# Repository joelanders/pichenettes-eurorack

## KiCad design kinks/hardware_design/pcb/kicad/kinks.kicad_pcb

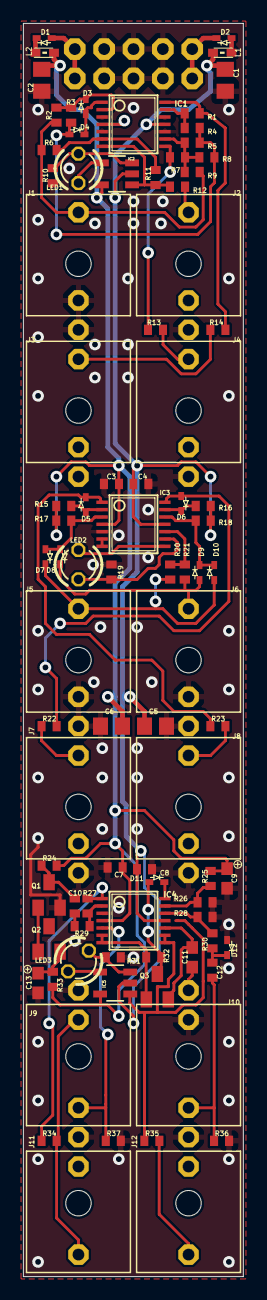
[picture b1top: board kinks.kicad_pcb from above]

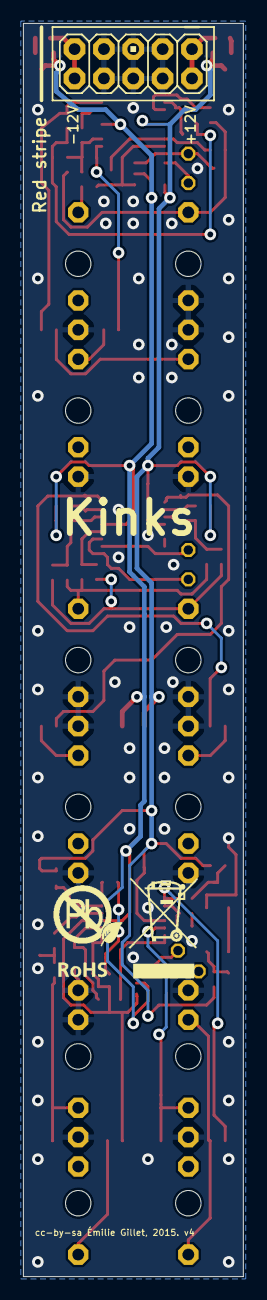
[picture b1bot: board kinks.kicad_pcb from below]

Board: 2 copper layers, 19.0 x 108.4 mm, 89 parts (2 on the bottom side), 56 nets.

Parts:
C1, C2, C5, C6: 22u; C0805
C3, C4, C7, C8, C10: 100n; C0402
C9, C13: 4.7u; C0603
C11: 10n; C0603
C12: 100p; C0402
D1, D2: PMEG2010AEB; SOD523
D3, D4, D5, D6, D7, D8, D9, D10, D11, D12: 1N4148; SOD523
IC1, IC3: TL074PW; TSSOP14
IC2, IC5: LM321MF; SOT23-5
IC4: OPA4171; TSSOP14
J1, J2, J3, J4, J5, J6, J7, J8, J9, J10, J11, J12: PJ301_THONKICONN6; WQP_PJ_301M6
JP1: M05X2PTH; AVR_ICSP
L1, L2: 0603
LED1, LED2, LED3: WP937EGW; LED3MM
Q1, Q2: MMBT3904; SOT23-BEC
Q3: MMBFJ309; SOT23
R1, R2, R6, R7, R9, R11: 200k; R0402
R3, R4, R5, R8, R28, R29, R36: 100k; R0402
R10, R19, R31: 1.0k; R0402
R12, R13, R14, R22, R23, R34, R35: 180; R0402
R15, R16, R17, R18: 220k; R0402
R20, R21, R25, R32, R37: 1.0M; R0402
R24: 4.7k; R0402
R26, R30: 10k; R0402
R27: 1.5M; R0402
R33: 470k; R0402
U$2: ROHS

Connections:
A: D7.C, D10.A, J5.P3, R20.2
B: D8.C, D9.A, J6.P3, R21.2
GND: C1.1, C2.2, C3.2, C4.1, C5.1, C6.2, C7.2, C8.1, C9.2, C11.2, C13.2, D12.A, IC1.3, IC1.5, IC1.10, IC1.12, IC3.5, IC4.3, J1.P1, J1.P2, J2.P1, J3.P1, J4.P1, J5.P1, J5.P2, J6.P1, J6.P2, J7.P1, J8.P1, J9.P1, J10.P1, J10.P2, J11.P1, J12.P1, JP1.3, JP1.4, JP1.5, JP1.6, JP1.7, JP1.8, Q1.E, R10.2, R19.2, R26.1, R28.1, R31.2, R36.1, R37.2
unnamed: D9.C, D10.C, IC3.12, R18.1
unnamed: D6.A, IC3.14, R22.2
unnamed: IC4.8, IC4.9, IC5.1, R35.2
unnamed: D6.C, IC3.13, R16.1
unnamed: D7.A, D8.A, IC3.3, R17.1
unnamed: D1.A, JP1.1, JP1.2
unnamed: IC3.6, IC3.7
unnamed: Q1.B, Q2.B
unnamed: IC2.3, LED1.K, R10.1
unnamed: D5.C, IC3.1, R23.2
unnamed: IC2.4, LED1.A
unnamed: C13.1, Q2.E, R33.2
unnamed: C10.2, R29.2
unnamed: IC3.8, LED2.K
unnamed: D5.A, IC3.2, R15.1
unnamed: IC4.2, R27.2, R29.1
unnamed: J8.P3, R23.1
unnamed: IC3.10, R20.1, R21.1
unnamed: IC5.3, LED3.A, R31.1
unnamed: D2.C, JP1.9, JP1.10
unnamed: IC1.6, R6.1, R11.2
unnamed: D1.C, L2.2
unnamed: IC1.7, IC2.1, R11.1, R12.2
unnamed: J2.P3, R12.1
unnamed: D3.C, IC1.2, R2.1, R3.2
unnamed: D3.A, D4.C, IC1.1
unnamed: IC1.14, R1.1, R14.2
unnamed: IC1.13, R1.2, R4.1
unnamed: IC3.9, LED2.A, R19.1
unnamed: IC5.4, LED3.K
unnamed: C10.1, Q1.C, R24.1
unnamed: J3.P3, R14.1
unnamed: IC1.9, R5.1, R7.2, R8.1, R9.1
unnamed: J4.P3, R13.1
unnamed: IC1.8, R7.1, R13.2
unnamed: IC4.1, R27.1, R34.2
unnamed: J9.P2, J11.P3, R34.1
unnamed: J1.P3, R2.2, R6.2, R9.2
unnamed: D4.A, R3.1, R4.2, R5.2, R8.2
unnamed: IC4.5, J9.P3, R37.1
unnamed: IC4.6, IC4.7, Q3.1, R32.2
unnamed: D11.A, Q3.3, R32.1
unnamed: D11.C, IC4.14
unnamed: D2.A, L1.2
unnamed: C11.1, IC4.10, Q3.2
unnamed: IC4.12, R28.2, R30.2
unnamed: J7.P3, R22.1
unnamed: J12.P3, R35.1
unnamed: C12.1, J10.P3, R36.2
unnamed: IC4.13, R25.1, R26.2
unnamed: C12.2, D12.C, R30.1
VCC: C2.1, C3.1, C6.1, C7.1, C9.1, IC1.4, IC2.5, IC3.4, IC4.4, IC5.5, L2.1, R15.2, R17.2, R24.2, R25.2, R33.1
VEE: C1.2, C4.2, C5.2, C8.2, IC1.11, IC2.2, IC3.11, IC4.11, IC5.2, L1.1, R16.2, R18.2

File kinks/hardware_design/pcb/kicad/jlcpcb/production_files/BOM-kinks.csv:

Comment,Designator,Footprint,LCSC
M05X2PTH,JP1,AVR_ICSP,
4.7u,C9,C0603,
PMEG2010AEB,D2,SOD523,
PMEG2010AEB,D1,SOD523,
WP937EGW,LED2,LED3MM,
1.0k,R19,R0402,
100n,C3,C0402,
100n,C4,C0402,
WP937EGW,LED3,LED3MM,
1.0k,R31,R0402,
LM321MF,IC5,SOT23-5,
100n,C7,C0402,
100n,C8,C0402,
PJ301_THONKICONN6,J1,WQP_PJ_301M6,
PJ301_THONKICONN6,J4,WQP_PJ_301M6,
PJ301_THONKICONN6,J2,WQP_PJ_301M6,
PJ301_THONKICONN6,J3,WQP_PJ_301M6,
PJ301_THONKICONN6,J8,WQP_PJ_301M6,
PJ301_THONKICONN6,J7,WQP_PJ_301M6,
PJ301_THONKICONN6,J5,WQP_PJ_301M6,
PJ301_THONKICONN6,J6,WQP_PJ_301M6,
PJ301_THONKICONN6,J12,WQP_PJ_301M6,
PJ301_THONKICONN6,J9,WQP_PJ_301M6,
PJ301_THONKICONN6,J10,WQP_PJ_301M6,
PJ301_THONKICONN6,J11,WQP_PJ_301M6,
TL074PW,IC3,TSSOP14,
1N4148,D10,SOD523,
1N4148,D9,SOD523,
220k,R18,R0402,
180,R22,R0402,
220k,R17,R0402,
180,R23,R0402,
1.0M,R20,R0402,
1.0M,R21,R0402,
WP937EGW,LED1,LED3MM,
1.0k,R10,R0402,
LM321MF,IC2,SOT23-5,
TL074PW,IC1,TSSOP14,
200k,R6,R0402,
200k,R11,R0402,
200k,R2,R0402,
100k,R3,R0402,
1N4148,D3,SOD523,
1N4148,D4,SOD523,
100k,R4,R0402,
200k,R1,R0402,
180,R14,R0402,
100k,R5,R0402,
200k,R7,R0402,
180,R13,R0402,
180,R12,R0402,
100k,R8,R0402,
200k,R9,R0402,
220k,R15,R0402,
OPA4171,IC4,TSSOP14,
100n,C10,C0402,
1.5M,R27,R0402,
100k,R29,R0402,
180,R34,R0402,
1.0M,R37,R0402,
MMBFJ309,Q3,SOT23,
1.0M,R32,R0402,
1N4148,D11,SOD523,
10n,C11,C0603,
180,R35,R0402,
100k,R36,R0402,
100p,C12,C0402,
1N4148,D12,SOD523,
10k,R30,R0402,
100k,R28,R0402,
10k,R26,R0402,
1.0M,R25,R0402,
22u,C2,C0805,
22u,C1,C0805,
,L2,0603,
,L1,0603,
MMBT3904,Q2,SOT23-BEC,
MMBT3904,Q1,SOT23-BEC,
470k,R33,R0402,
4.7k,R24,R0402,
4.7u,C13,C0603,
22u,C6,C0805,
22u,C5,C0805,
1N4148,D6,SOD523,
220k,R16,R0402,
1N4148,D7,SOD523,
1N4148,D8,SOD523,
1N4148,D5,SOD523,

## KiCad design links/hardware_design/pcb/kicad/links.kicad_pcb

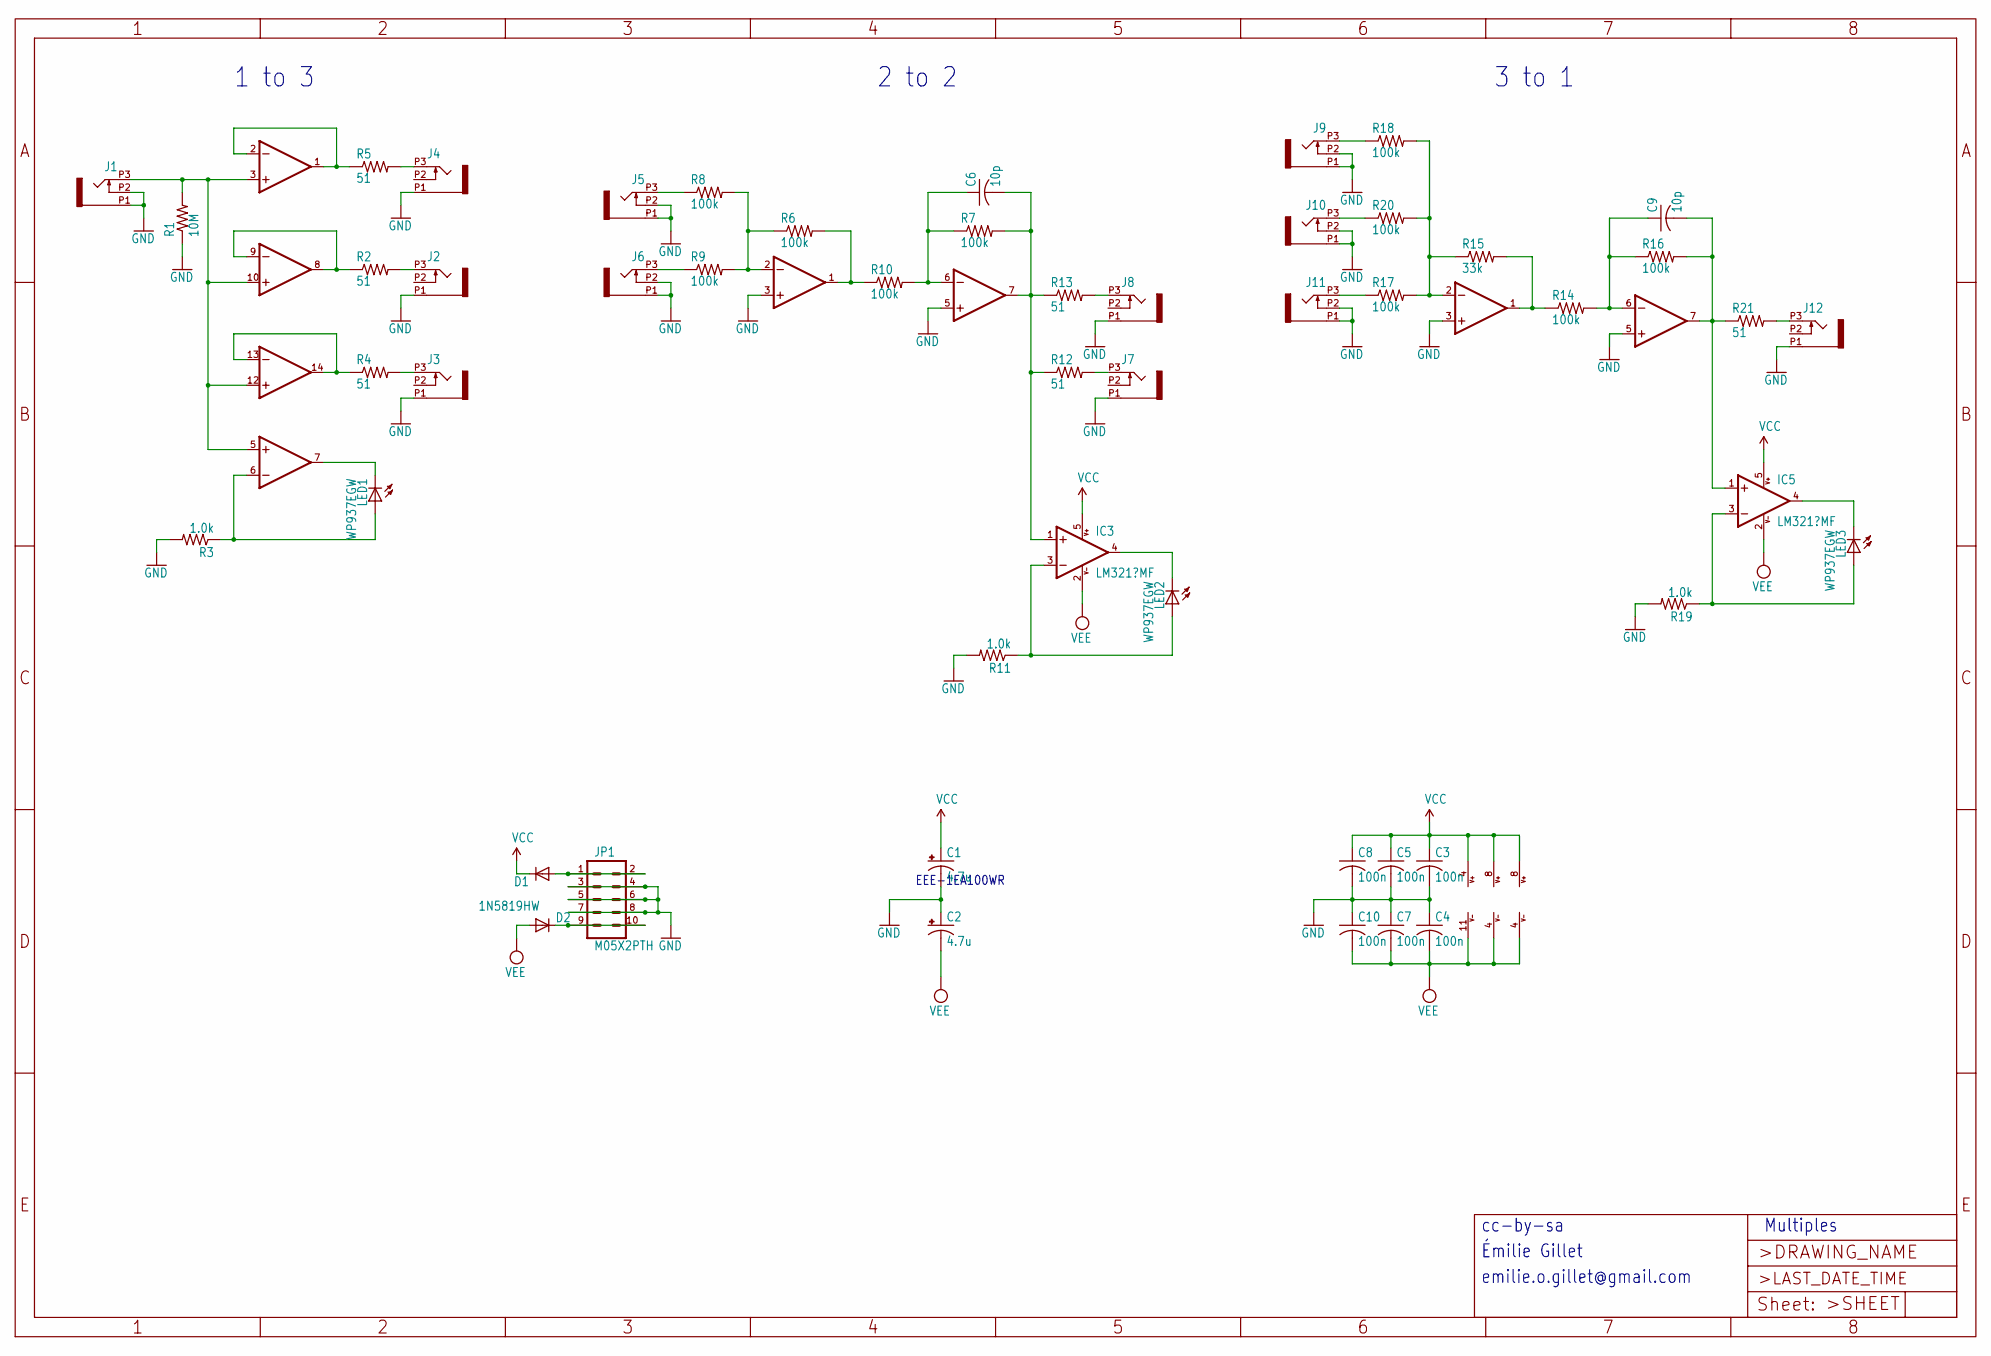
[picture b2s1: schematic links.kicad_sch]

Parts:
C1, C2: 4.7u; CP_Elec_3x5.3
C3, C4, C5, C7, C8, C10: 100n; C0603
C6, C9: 10p; C0603
D1, D2: 1N5819HW; SOD123
IC1: OPA4171; TSSOP14
IC2, IC4: TL072PW; TSSOP8
IC3, IC5: LM321?MF; SOT23-5
J1, J2, J3, J4, J5, J6, J7, J8, J9, J10, J11, J12: PJ301_THONKICONN6; WQP_PJ_301M6
JP1: M05X2PTH; AVR_ICSP
LED1, LED2, LED3: WP937EGW; LED3MM
R1: 10M; R0603
R2, R4, R5, R12, R13, R21: 51; R0603
R3, R11, R19: 1.0k; R0603
R6, R7, R8, R9, R10, R14, R16, R17, R18, R20: 100k; R0603
R15: 33k; R0603

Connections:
GND: C1.2, C2.1, C3.2, C4.1, C5.2, C7.1, C8.2, C10.1, IC2.3 (+IN), IC2.5 (+IN), IC4.3 (+IN), IC4.5 (+IN), J1.P1 (1), J1.P2 (2), J2.P1 (1), J3.P1 (1), J4.P1 (1), J5.P1 (1), J5.P2 (2), J6.P1 (1), J6.P2 (2), J7.P1 (1), J8.P1 (1), J9.P1 (1), J9.P2 (2), J10.P1 (1), J10.P2 (2), J11.P1 (1), J11.P2 (2), J12.P1 (1), JP1.3, JP1.4, JP1.5, JP1.6, JP1.7, JP1.8, R1.1, R3.2, R11.2, R19.2
unnamed: D1.A, JP1.1, JP1.2
unnamed: D2.C, JP1.9, JP1.10
unnamed: IC1.3 (+IN), IC1.5 (+IN), IC1.10 (+IN), IC1.12 (+IN), J1.P3 (3), R1.2
unnamed: IC1.1 (OUT), IC1.2 (-IN), R5.1
unnamed: IC1.6 (-IN), LED1.A, R3.1
unnamed: IC1.7 (OUT), LED1.K (C)
unnamed: IC1.8 (OUT), IC1.9 (-IN), R2.1
unnamed: IC1.13 (-IN), IC1.14 (OUT), R4.1
unnamed: IC2.2 (-IN), R6.1, R8.2, R9.2
unnamed: IC2.1 (OUT), R6.2, R10.1
unnamed: C6.1, IC2.6 (-IN), R7.1, R10.2
unnamed: C6.2, IC2.7 (OUT), IC3.1 (+IN), R7.2, R12.1, R13.1
unnamed: IC3.3 (-IN), LED2.A, R11.1
unnamed: IC3.4 (OUT), LED2.K (C)
unnamed: IC4.2 (-IN), R15.1, R17.2, R18.2, R20.2
unnamed: IC4.1 (OUT), R14.1, R15.2
unnamed: C9.1, IC4.6 (-IN), R14.2, R16.1
unnamed: C9.2, IC4.7 (OUT), IC5.1 (+IN), R16.2, R21.1
unnamed: IC5.3 (-IN), LED3.A, R19.1
unnamed: IC5.4 (OUT), LED3.K (C)
unnamed: J2.P3 (3), R2.2
unnamed: J3.P3 (3), R4.2
unnamed: J4.P3 (3), R5.2
unnamed: J5.P3 (3), R8.1
unnamed: J6.P3 (3), R9.1
unnamed: J7.P3 (3), R12.2
unnamed: J8.P3 (3), R13.2
unnamed: J9.P3 (3), R18.1
unnamed: J10.P3 (3), R20.1
unnamed: J11.P3 (3), R17.1
unnamed: J12.P3 (3), R21.2
VCC: C1.1, C3.1, C5.1, C8.1, D1.C, IC1.4 (V+), IC2.8 (V+), IC3.5 (V+), IC4.8 (V+), IC5.5 (V+)
VEE: C2.2, C4.2, C7.2, C10.2, D2.A, IC1.11 (V-), IC2.4 (V-), IC3.2 (V-), IC4.4 (V-), IC5.2 (V-)

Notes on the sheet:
Multiples
EEE-1EA100WR
1 to 3
cc-by-sa
3 to 1
2 to 2
emilie.o.gillet@gmail.com
Émilie Gillet

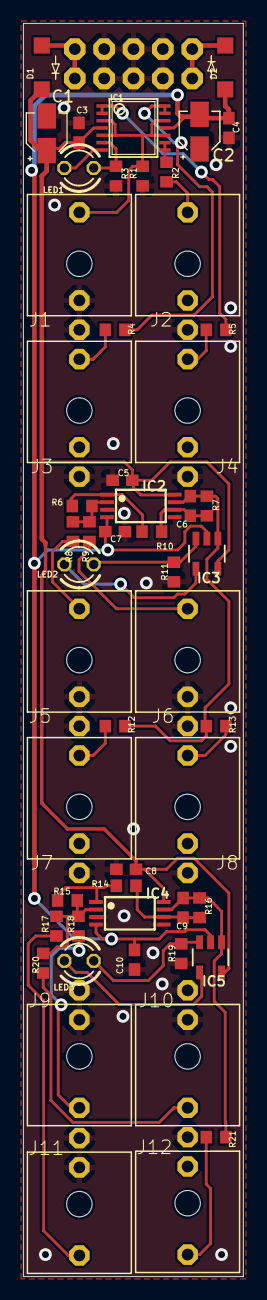
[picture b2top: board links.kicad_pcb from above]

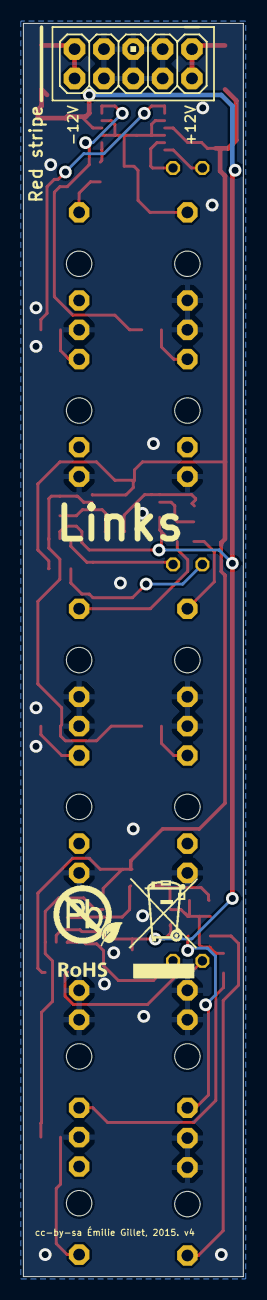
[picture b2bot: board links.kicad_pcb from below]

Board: 2 copper layers, 19.0 x 108.4 mm, 55 parts (2 on the bottom side), 34 nets.

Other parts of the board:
U$2: ROHS

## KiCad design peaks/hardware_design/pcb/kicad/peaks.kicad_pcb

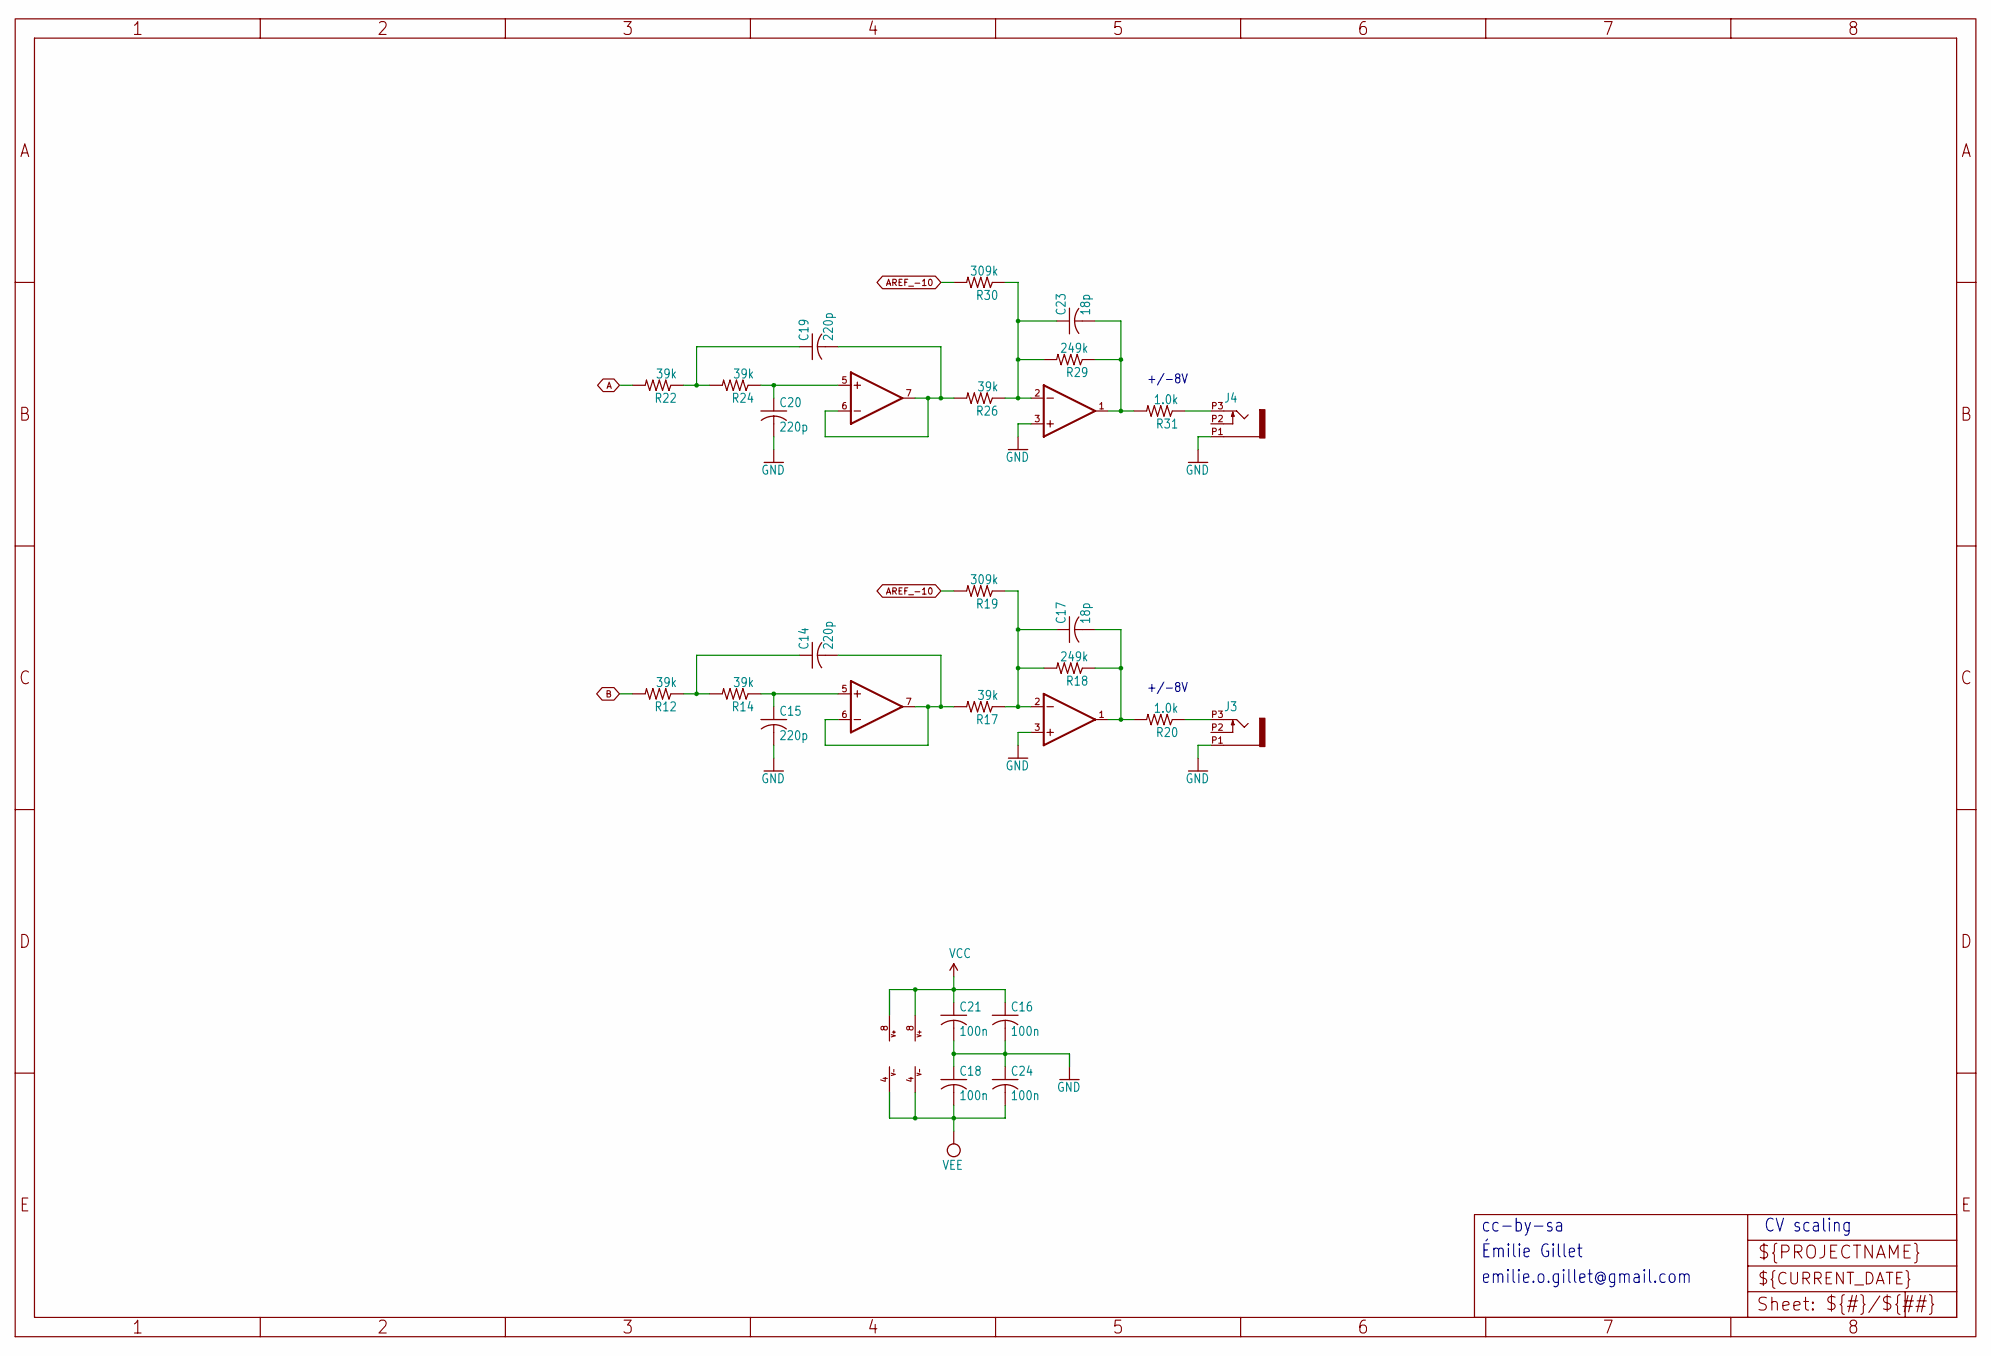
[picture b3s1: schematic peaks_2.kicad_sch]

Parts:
C14, C15, C19, C20: 220p; C0603
C16, C18, C21, C24: 100n; C0603
C17, C23: 18p; C0603
IC4, IC5: TL072D; SO08
J3, J4: PJ301_THONKICONN6; WQP_PJ_301M6
R12, R14, R17, R22, R24, R26: 39k; R0603
R18, R29: 249k; R0603
R19, R30: 309k; R0603
R20, R31: 1.0k; R0603

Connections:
A: R22.2; also elsewhere on the board
AREF_-10: R19.2, R30.2; also elsewhere on the board
B: R12.2; also elsewhere on the board
GND: C15.2, C16.2, C18.1, C20.2, C21.2, C24.1, IC4.3 (+IN), IC5.3 (+IN), J3.P1 (1), J4.P1 (1); also elsewhere on the board
unnamed: C14.1, R12.1, R14.2
unnamed: C19.1, R22.1, R24.2
unnamed: C17.1, IC4.2 (-IN), R17.1, R18.2, R19.1
unnamed: C17.2, IC4.1 (OUT), R18.1, R20.2
unnamed: C15.1, IC4.5 (+IN), R14.1
unnamed: C14.2, IC4.6 (-IN), IC4.7 (OUT), R17.2
unnamed: C23.1, IC5.2 (-IN), R26.1, R29.2, R30.1
unnamed: C23.2, IC5.1 (OUT), R29.1, R31.2
unnamed: C20.1, IC5.5 (+IN), R24.1
unnamed: C19.2, IC5.6 (-IN), IC5.7 (OUT), R26.2
unnamed: J3.P3 (3), R20.1
unnamed: J4.P3 (3), R31.1
VCC: C16.1, C21.1, IC4.8 (V+), IC5.8 (V+); also elsewhere on the board
VEE: C18.2, C24.2, IC4.4 (V-), IC5.4 (V-); also elsewhere on the board

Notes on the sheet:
Émilie Gillet
cc-by-sa
+/-8V
emilie.o.gillet@gmail.com
CV scaling

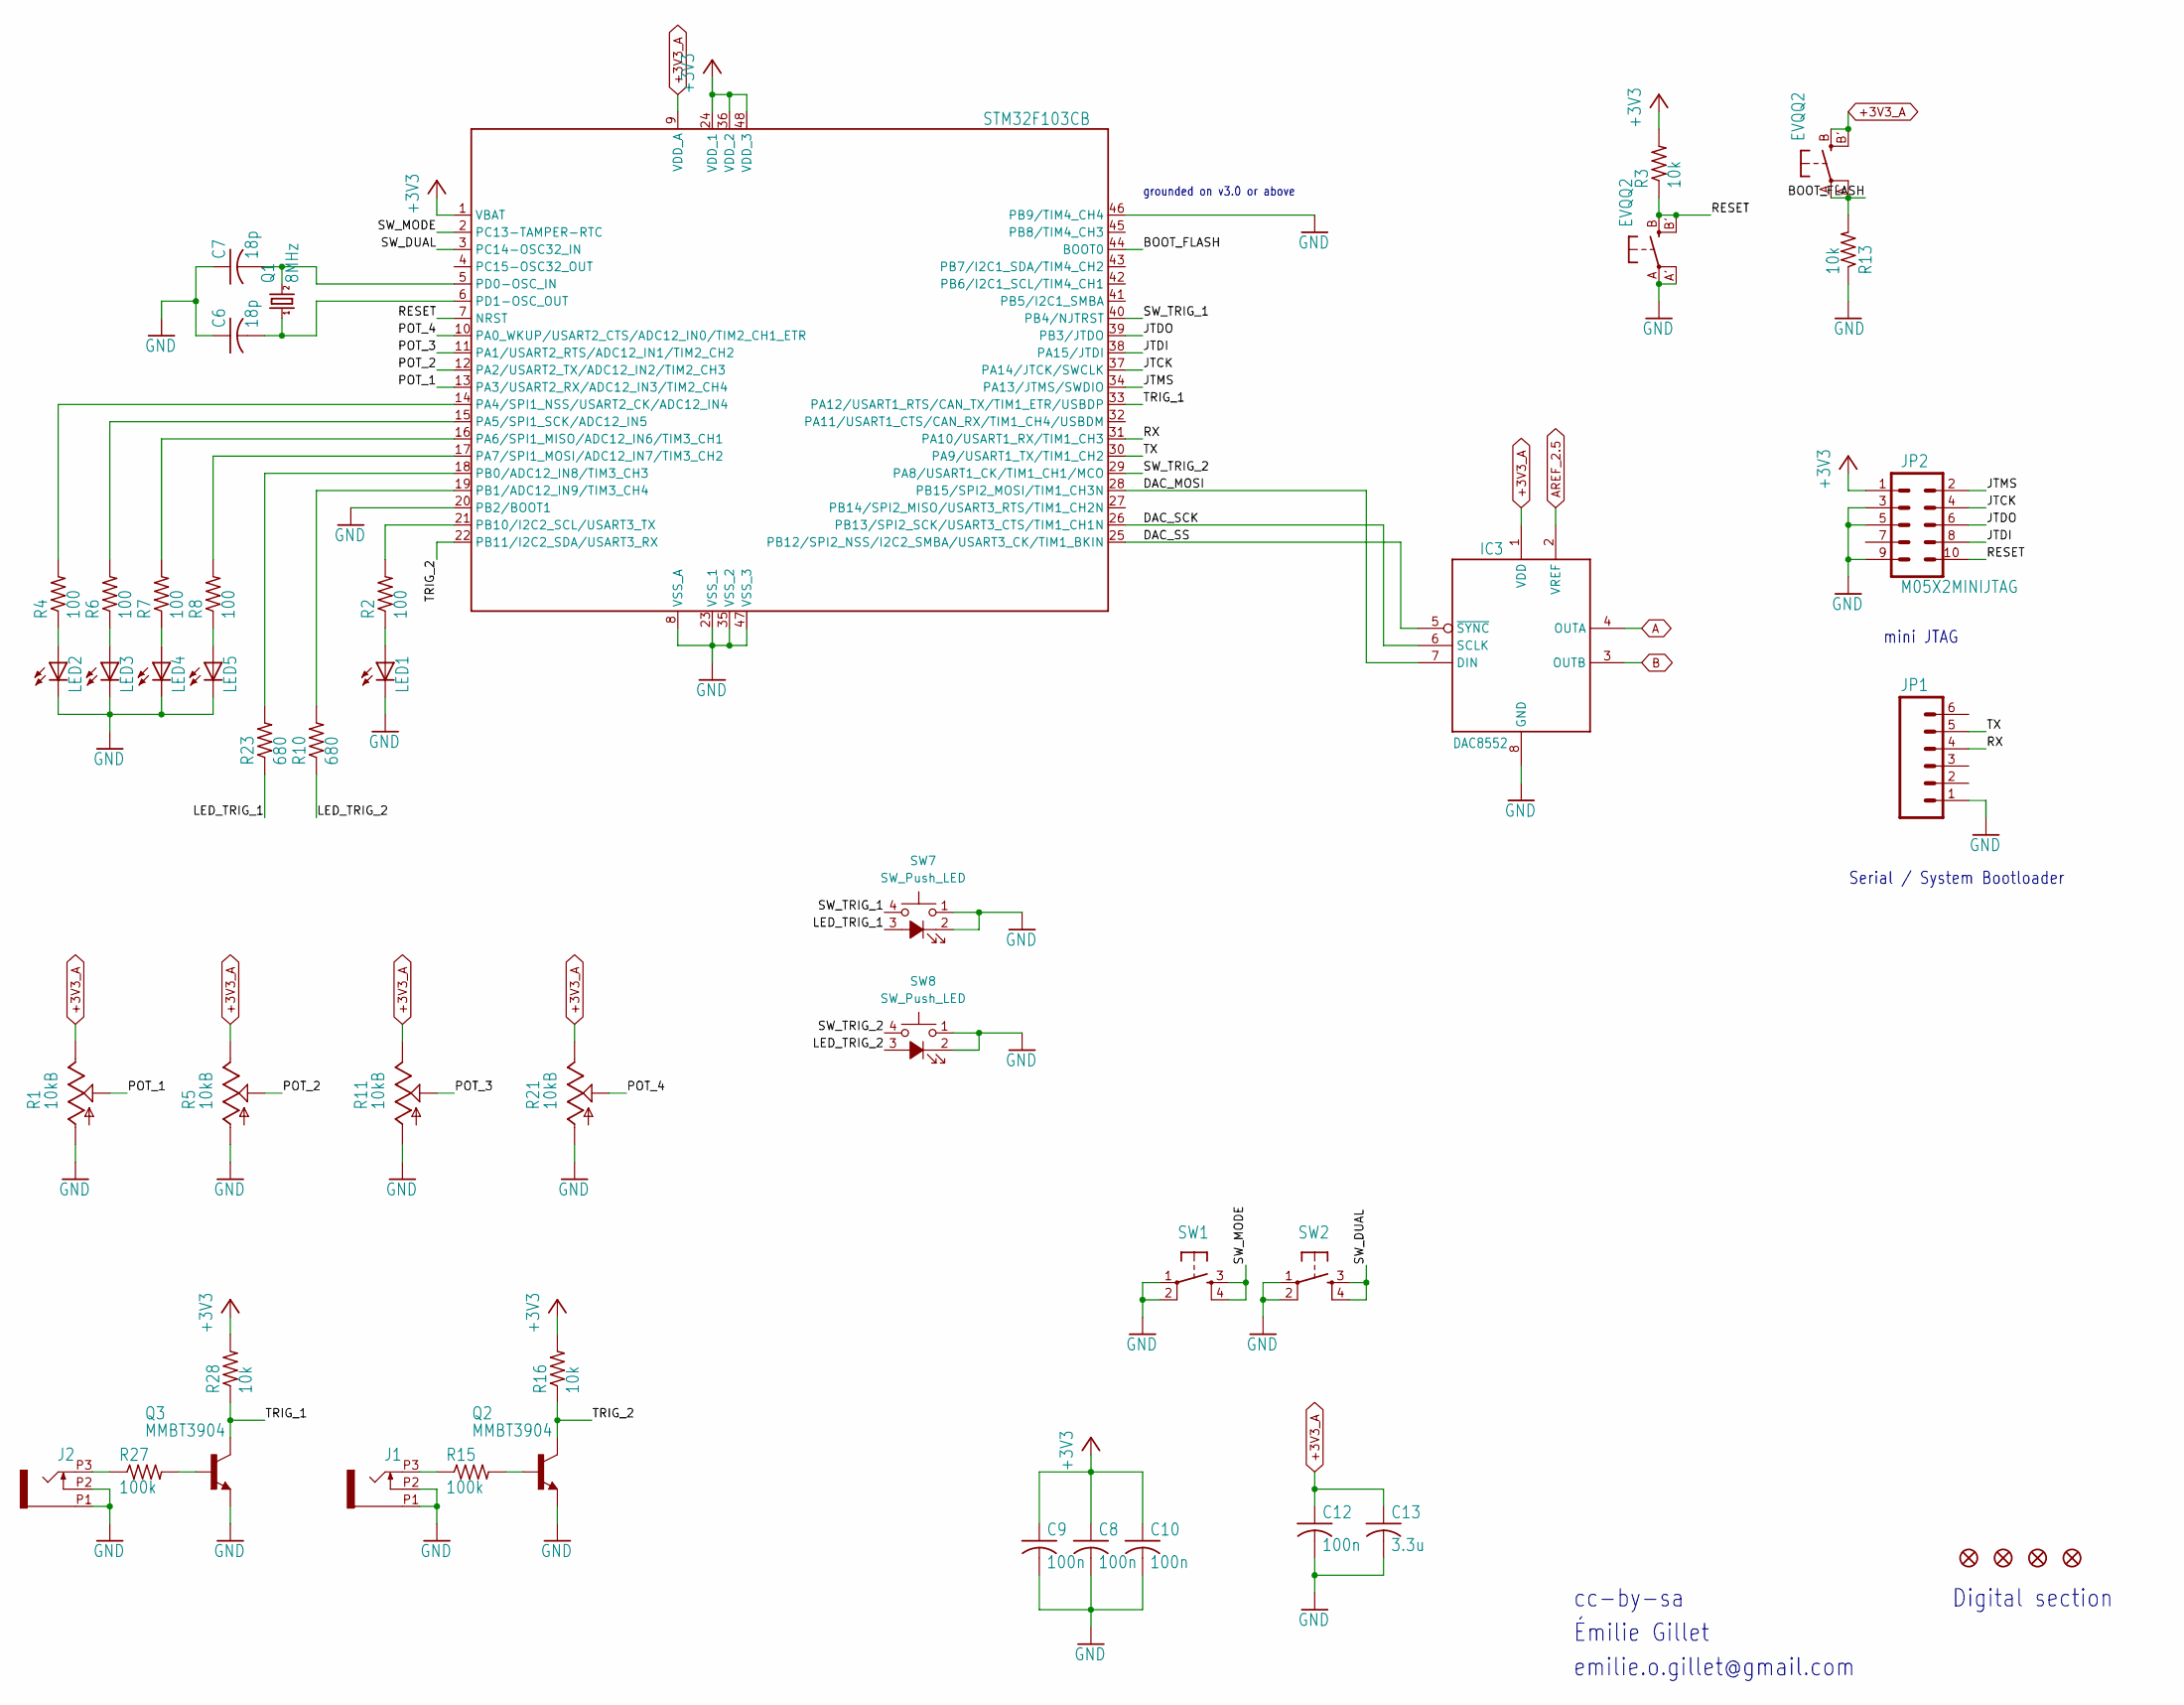
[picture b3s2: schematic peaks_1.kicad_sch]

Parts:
C6, C7: 18p; C0603
C8, C9, C10, C12: 100n; C0603
C13: 3.3u; C0603
F1, F2, F3, F4: FIDUCIAL1X2; FIDUCIAL-1X2
IC3: DAC8552; MSOP-8
J1, J2: PJ301_THONKICONN6; WQP_PJ_301M6
JP1: M06SIP; 1X06
JP2: M05X2MINIJTAG; 2X5-1.27
LED1, LED2, LED3, LED4, LED5: LED3MM
Q1: 8MHz; HC49UP
Q2, Q3: MMBT3904; SOT23-BEC
R1, R5, R11, R21: 10kB; ALPS_POT_VERTICAL_PS
R2, R4, R6, R7, R8: 100; R0603
R3, R13, R16, R28: 10k; R0603
R10, R23: 680; R0603
R15, R27: 100k; R0603
SW1, SW2: TAC_SWITCHPTH; TACTILE-PTH
SW3, SW5: EVQQ2; k2-1808 pushbutton switch
SW7, SW8: SW_Push_LED; C&K_D6R
UC1: STM32F103CB; LQFP48

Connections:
+3V3: C8.1, C9.1, C10.1, JP2.1, R3.2, R16.2, R28.2, UC1.1 (VBAT), UC1.24 (VDD_1), UC1.36 (VDD_2), UC1.48 (VDD_3); also elsewhere on the board
+3V3_A: C12.1, C13.1, IC3.1 (VDD), R1.P$1 (E), R5.P$1 (E), R11.P$1 (E), R21.P$1 (E), SW5.B (S), SW5.B' (S1), UC1.9 (VDD_A); also elsewhere on the board
/peaks_1/BOOT_FLASH: R13.2, SW5.A, SW5.A' (P1), UC1.44 (BOOT0)
/peaks_1/DAC_MOSI: IC3.7 (DIN), UC1.28 (PB15/SPI2_MOSI/TIM1_CH3N)
/peaks_1/DAC_SCK: IC3.6 (SCLK), UC1.26 (PB13/SPI2_SCK/USART3_CTS/TIM1_CH1N)
/peaks_1/DAC_SS: IC3.5 (~SYNC), UC1.25 (PB12/SPI2_NSS/I2C2_SMBA/USART3_CK/TIM1_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)
/peaks_1/JTCK: JP2.4, UC1.37 (PA14/JTCK/SWCLK)
/peaks_1/JTDI: JP2.8, UC1.38 (PA15/JTDI)
/peaks_1/JTDO: JP2.6, UC1.39 (PB3/JTDO)
/peaks_1/JTMS: JP2.2, UC1.34 (PA13/JTMS/SWDIO)
/peaks_1/LED_TRIG_1: R23.1, SW7.3
/peaks_1/LED_TRIG_2: R10.1, SW8.3
/peaks_1/POT_1: R1.P$2 (S), UC1.13 (PA3/USART2_RX/ADC12_IN3/TIM2_CH4)
/peaks_1/POT_2: R5.P$2 (S), UC1.12 (PA2/USART2_TX/ADC12_IN2/TIM2_CH3)
/peaks_1/POT_3: R11.P$2 (S), UC1.11 (PA1/USART2_RTS/ADC12_IN1/TIM2_CH2)
/peaks_1/POT_4: R21.P$2 (S), UC1.10 (PA0_WKUP/USART2_CTS/ADC12_IN0/TIM2_CH1_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)
/peaks_1/RESET: JP2.10, R3.1, SW3.B (S), SW3.B' (S1), UC1.7 (NRST)
/peaks_1/RX: JP1.4, UC1.31 (PA10/USART1_RX/TIM1_CH3)
/peaks_1/SW_DUAL: SW2.3, SW2.4, UC1.3 (PC14-OSC32_IN)
/peaks_1/SW_MODE: SW1.3, SW1.4, UC1.2 (PC13-TAMPER-RTC)
/peaks_1/SW_TRIG_1: SW7.4, UC1.40 (PB4/NJTRST)
/peaks_1/SW_TRIG_2: SW8.4, UC1.29 (PA8/USART1_CK/TIM1_CH1/MCO)
/peaks_1/TRIG_1: Q3.C, R28.1, UC1.33 (PA12/USART1_RTS/CAN_TX/TIM1_ETR/USBDP)
/peaks_1/TRIG_2: Q2.C, R16.1, UC1.22 (PB11/I2C2_SDA/USART3_RX)
/peaks_1/TX: JP1.5, UC1.30 (PA9/USART1_TX/TIM1_CH2)
A: IC3.4 (OUTA); also elsewhere on the board
AREF_2.5: IC3.2 (VREF); also elsewhere on the board
B: IC3.3 (OUTB); also elsewhere on the board
GND: C6.1, C7.1, C8.2, C9.2, C10.2, C12.2, C13.2, IC3.8 (GND), J1.P1 (1), J1.P2 (2), J2.P1 (1), J2.P2 (2), JP1.1, JP2.3, JP2.5, JP2.9, LED1.K (C), LED2.K (C), LED3.K (C), LED4.K (C), LED5.K (C), Q2.E, Q3.E, R1.P$3 (A), R5.P$3 (A), R11.P$3 (A), R13.1, R21.P$3 (A), SW1.1, SW1.2, SW2.1, SW2.2, SW3.A, SW3.A' (P1), SW7.1, SW7.2, SW8.1, SW8.2, UC1.8 (VSS_A), UC1.20 (PB2/BOOT1), UC1.23 (VSS_1), UC1.35 (VSS_2), UC1.46 (PB9/TIM4_CH4), UC1.47 (VSS_3); also elsewhere on the board
unnamed: J1.P3 (3), R15.1
unnamed: J2.P3 (3), R27.1
unnamed: LED1.A, R2.1
unnamed: LED2.A, R4.1
unnamed: LED3.A, R6.1
unnamed: LED4.A, R7.1
unnamed: LED5.A, R8.1
unnamed: Q2.B, R15.2
unnamed: Q3.B, R27.2
unnamed: R4.2, UC1.14 (PA4/SPI1_NSS/USART2_CK/ADC12_IN4)
unnamed: R6.2, UC1.15 (PA5/SPI1_SCK/ADC12_IN5)
unnamed: R7.2, UC1.16 (PA6/SPI1_MISO/ADC12_IN6/TIM3_CH1)
unnamed: R8.2, UC1.17 (PA7/SPI1_MOSI/ADC12_IN7/TIM3_CH2)
unnamed: R23.2, UC1.18 (PB0/ADC12_IN8/TIM3_CH3)
unnamed: R10.2, UC1.19 (PB1/ADC12_IN9/TIM3_CH4)
unnamed: R2.2, UC1.21 (PB10/I2C2_SCL/USART3_TX)
unnamed: C7.2, Q1.2, UC1.5 (PD0-OSC_IN)
unnamed: C6.2, Q1.1, UC1.6 (PD1-OSC_OUT)

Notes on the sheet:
cc-by-sa
Émilie Gillet
Digital section
grounded on v3.0 or above
Serial / System Bootloader
emilie.o.gillet@gmail.com
mini JTAG

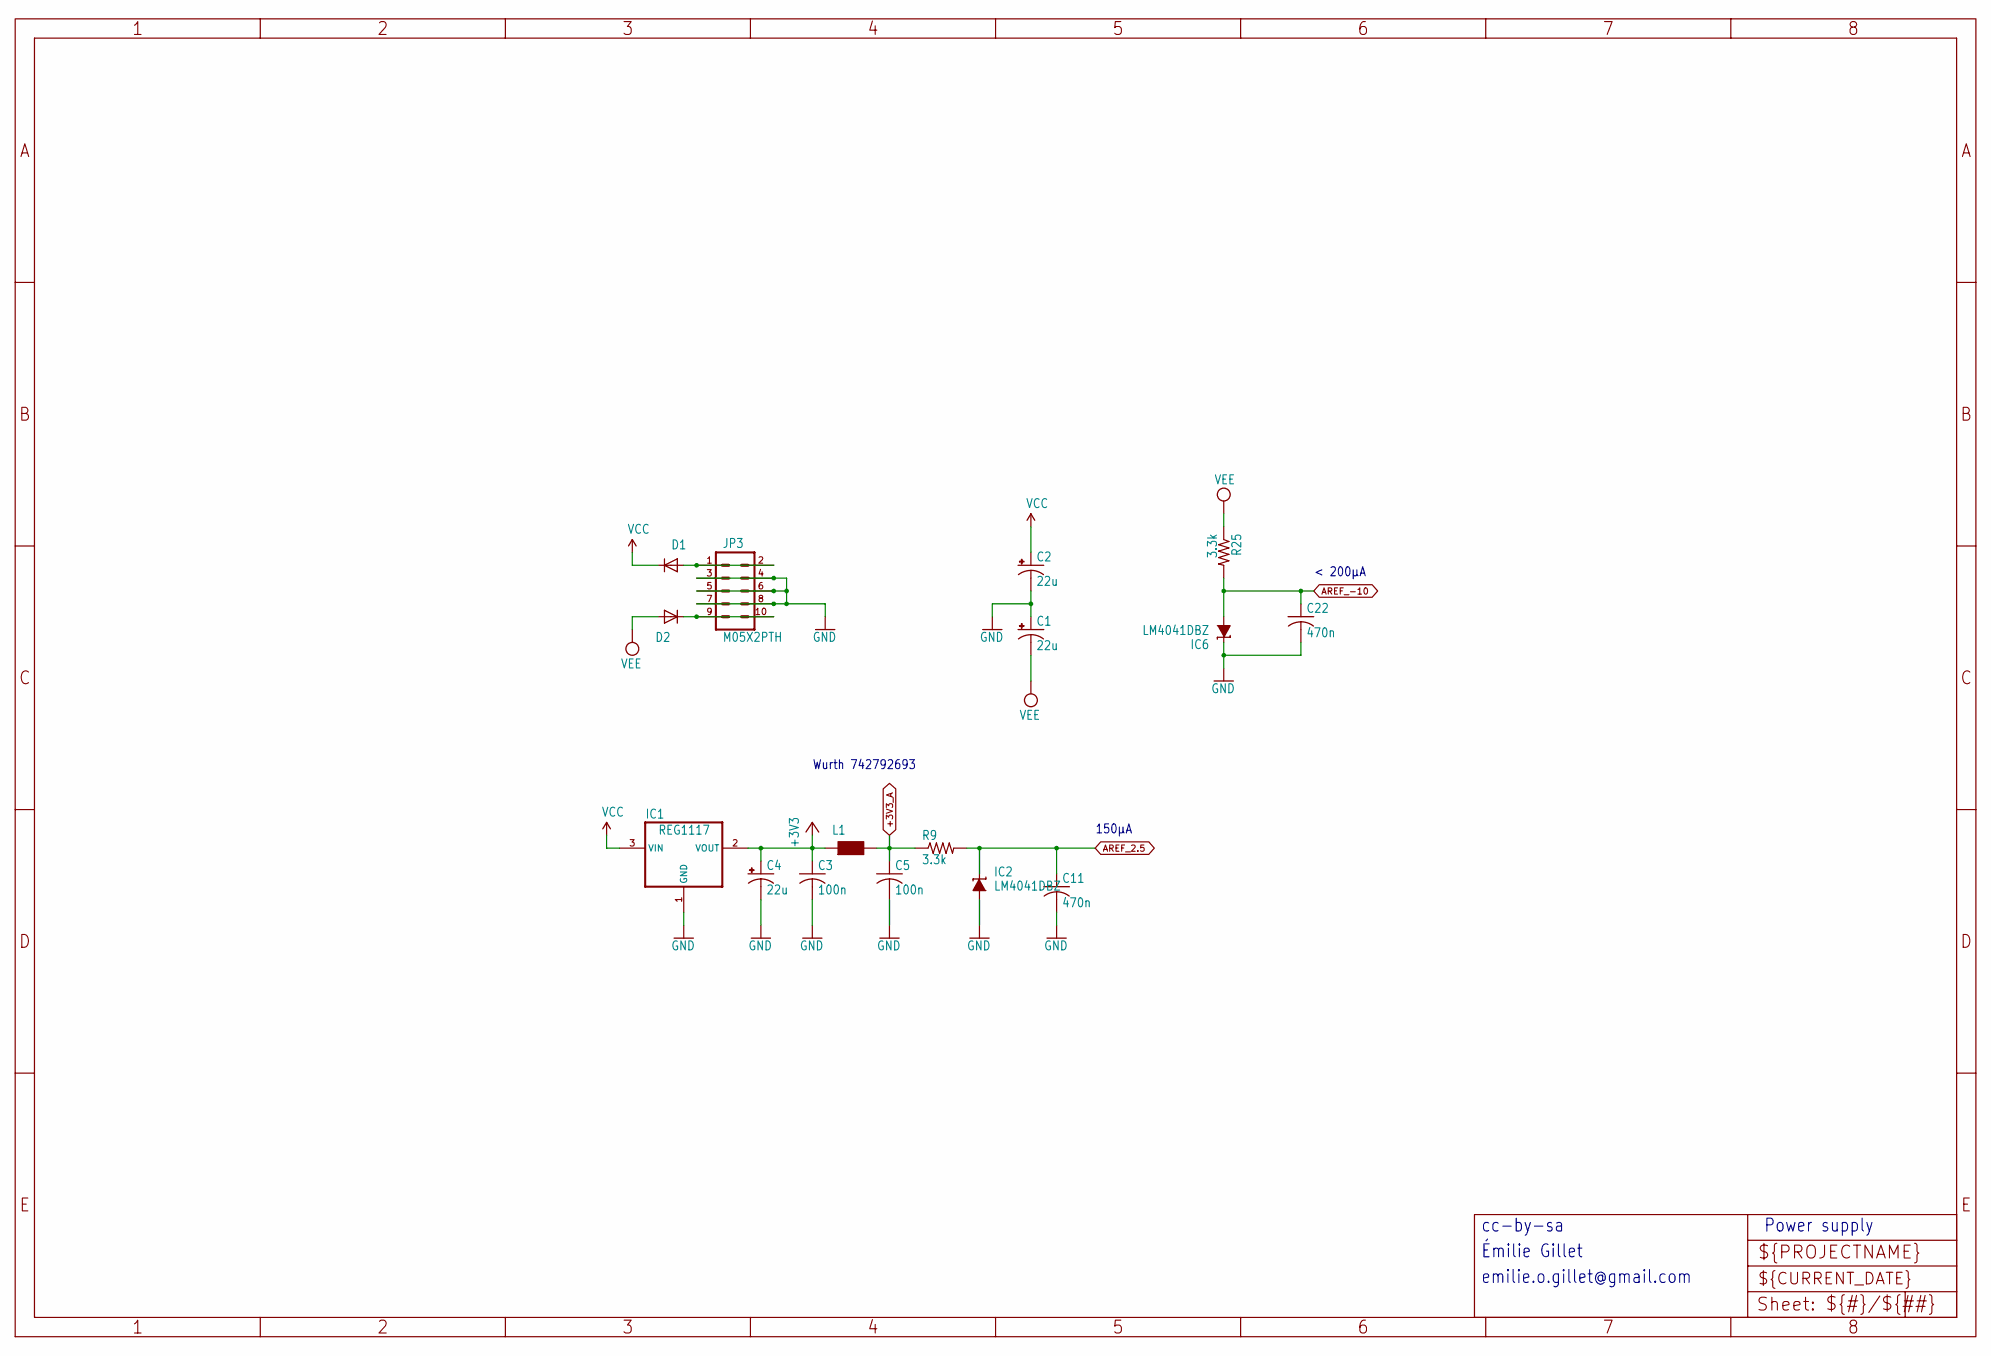
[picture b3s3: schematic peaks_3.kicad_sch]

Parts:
C1, C2, C4: 22u; PANASONIC_C
C3, C5: 100n; C0603
C11, C22: 470n; C0603
D1, D2: 1N5819HW; SOD123
IC1: REG1117; SOT223
IC2, IC6: LM4041DBZ; DBZ_R-PDSO-G3
JP3: M05X2PTH; AVR_ICSP
L1: WE-CBF_0603; 0603
R9, R25: 3.3k; R0603

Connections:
+3V3: C3.1, C4.+, IC1.2 (VOUT), L1.1; also elsewhere on the board
+3V3_A: C5.1, L1.2, R9.1; also elsewhere on the board
AREF_2.5: C11.1, IC2.1 (C), R9.2; also elsewhere on the board
AREF_-10: C22.1, IC6.2 (A), R25.2; also elsewhere on the board
GND: C1.+, C2.-, C3.2, C4.-, C5.2, C11.2, C22.2, IC1.1 (GND), IC2.2 (A), IC6.1 (C), JP3.3, JP3.4, JP3.5, JP3.6, JP3.7, JP3.8; also elsewhere on the board
unnamed: D1.A, JP3.1, JP3.2
unnamed: D2.C, JP3.9, JP3.10
VCC: C2.+, D1.C, IC1.3 (VIN); also elsewhere on the board
VEE: C1.-, D2.A, R25.1; also elsewhere on the board

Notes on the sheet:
Émilie Gillet
Power supply
< 200µA
150µA
Wurth 742792693
cc-by-sa
emilie.o.gillet@gmail.com

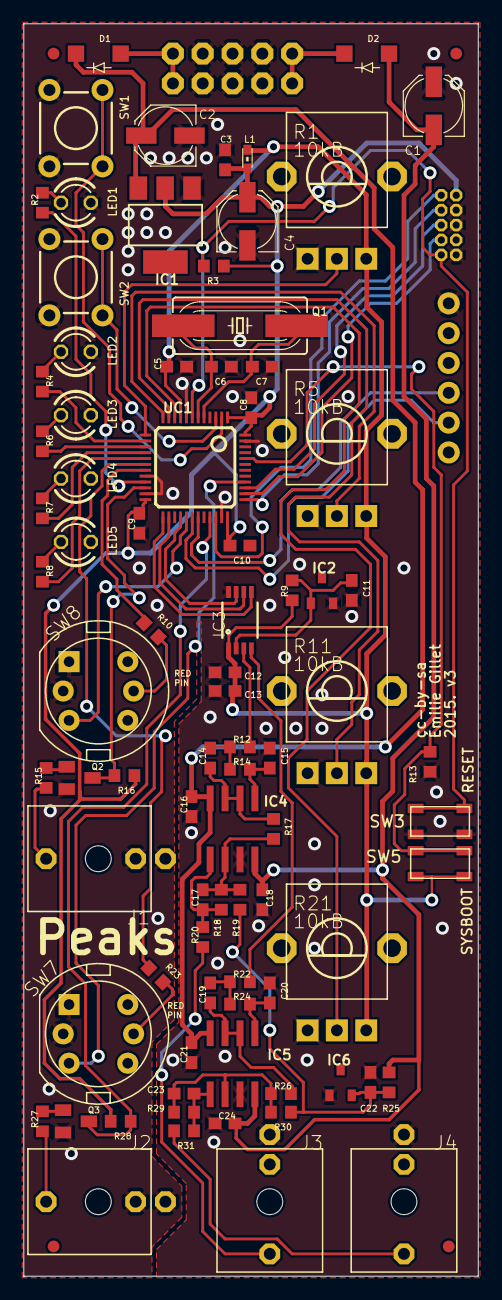
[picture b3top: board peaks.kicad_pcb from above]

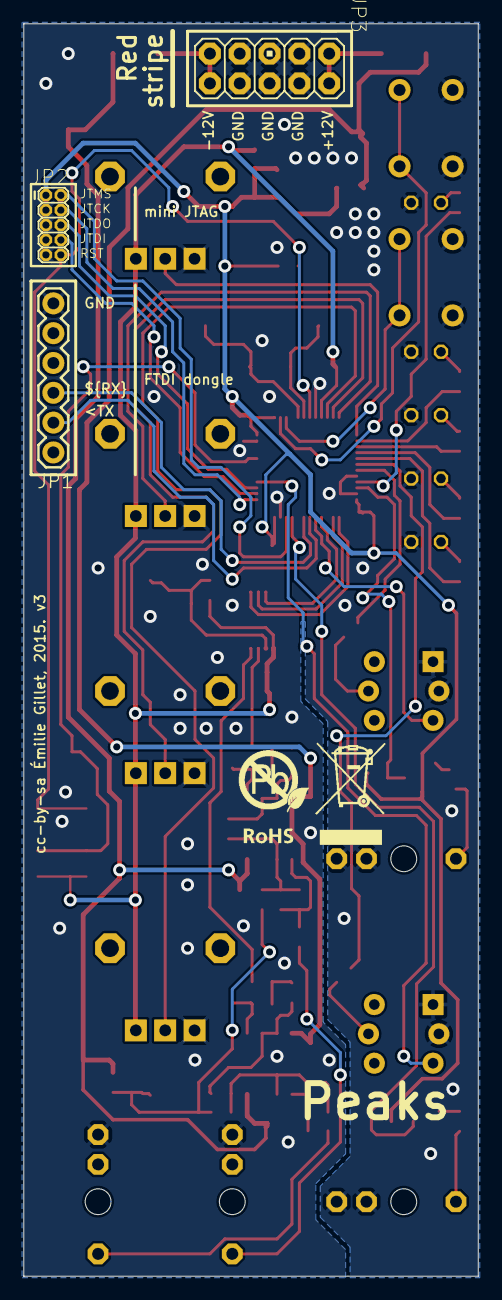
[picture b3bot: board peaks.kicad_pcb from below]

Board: 2 copper layers, 38.7 x 106.7 mm, 91 parts (4 on the bottom side), 64 nets.

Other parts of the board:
U$2: ROHS

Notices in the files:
kinks/hardware_design/pcb/kicad/kinks.kicad_pcb:
cc-by-sa Émilie Gillet, 2015. v4
peaks/hardware_design/pcb/kicad/peaks.kicad_pcb:
cc-by-sa Émilie Gillet, 2015. v3
